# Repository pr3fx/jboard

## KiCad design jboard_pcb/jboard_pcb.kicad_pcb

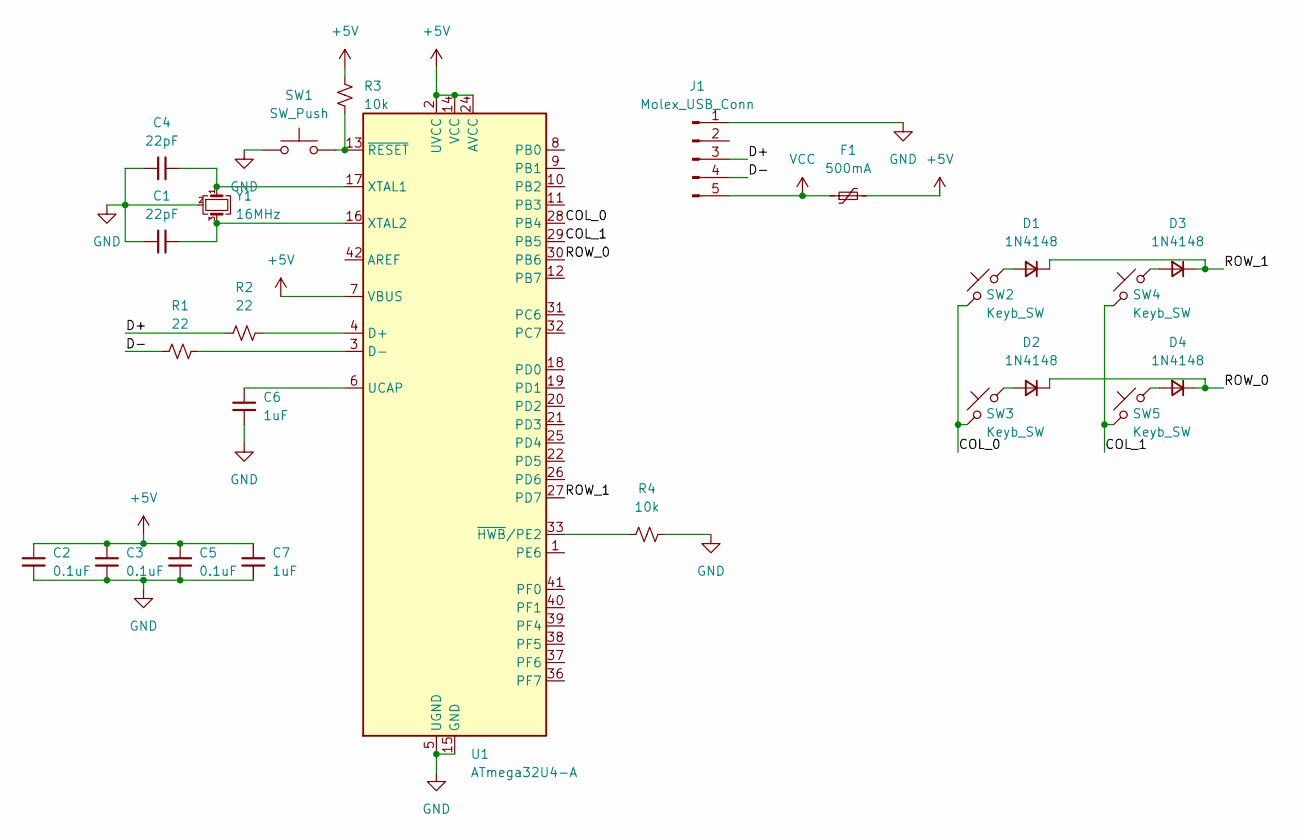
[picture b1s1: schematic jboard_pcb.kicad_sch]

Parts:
C1, C4: 22pF; C_0805_2012Metric
C2, C3, C5: 0.1uF; C_0805_2012Metric
C6, C7: 1uF; C_0805_2012Metric
D1, D2, D3, D4: 1N4148; D_SOD-123
F1: 500mA; Fuse_1206_3216Metric
J1: Molex_USB_Conn; Molex-0548190589
R1, R2: 22; R_0805_2012Metric
R3, R4: 10k; R_0805_2012Metric
SW1: SW_Push; SW_SPST_SKQG_WithoutStem
SW2, SW3, SW4, SW5: Keyb_SW; Kailh-PG1353-Solderable-1U
U1: ATmega32U4-A; TQFP-44_10x10mm_P0.8mm
Y1: 16MHz; Crystal_SMD_3225-4Pin_3.2x2.5mm

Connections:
+5V: C2.1, C3.1, C5.1, C7.1, F1.2, R3.1, U1.2 (UVCC), U1.7 (VBUS), U1.14 (VCC), U1.24 (AVCC), U1.34 (VCC), U1.44 (AVCC)
/COL_0: SW2.1, SW3.1, U1.28 (PB4)
/COL_1: SW4.1, SW5.1, U1.29 (PB5)
/D+: J1.3, R2.1
/D-: J1.4, R1.1
/ROW_0: D2.1 (K), D4.1 (K), U1.30 (PB6)
/ROW_1: D1.1 (K), D3.1 (K), U1.27 (PD7)
GND: C1.1, C2.2, C3.2, C4.1, C5.2, C6.2, C7.2, J1.1, R4.2, SW1.1, U1.5 (UGND), U1.15 (GND), U1.23 (GND), U1.35 (GND), U1.43 (GND), Y1.2 (G), Y1.4 (G)
unnamed: D1.2 (A), SW2.2
unnamed: D2.2 (A), SW3.2
unnamed: D3.2 (A), SW4.2
unnamed: D4.2 (A), SW5.2
unnamed: R2.2, U1.4 (D+)
unnamed: R1.2, U1.3 (D-)
unnamed: C6.1, U1.6 (UCAP)
unnamed: C4.2, U1.17 (XTAL1), Y1.1
unnamed: C1.2, U1.16 (XTAL2), Y1.3
unnamed: R4.1, U1.33 (~HWB/PE2)
unnamed: R3.2, SW1.2, U1.13 (~RESET)
VCC: F1.1, J1.5

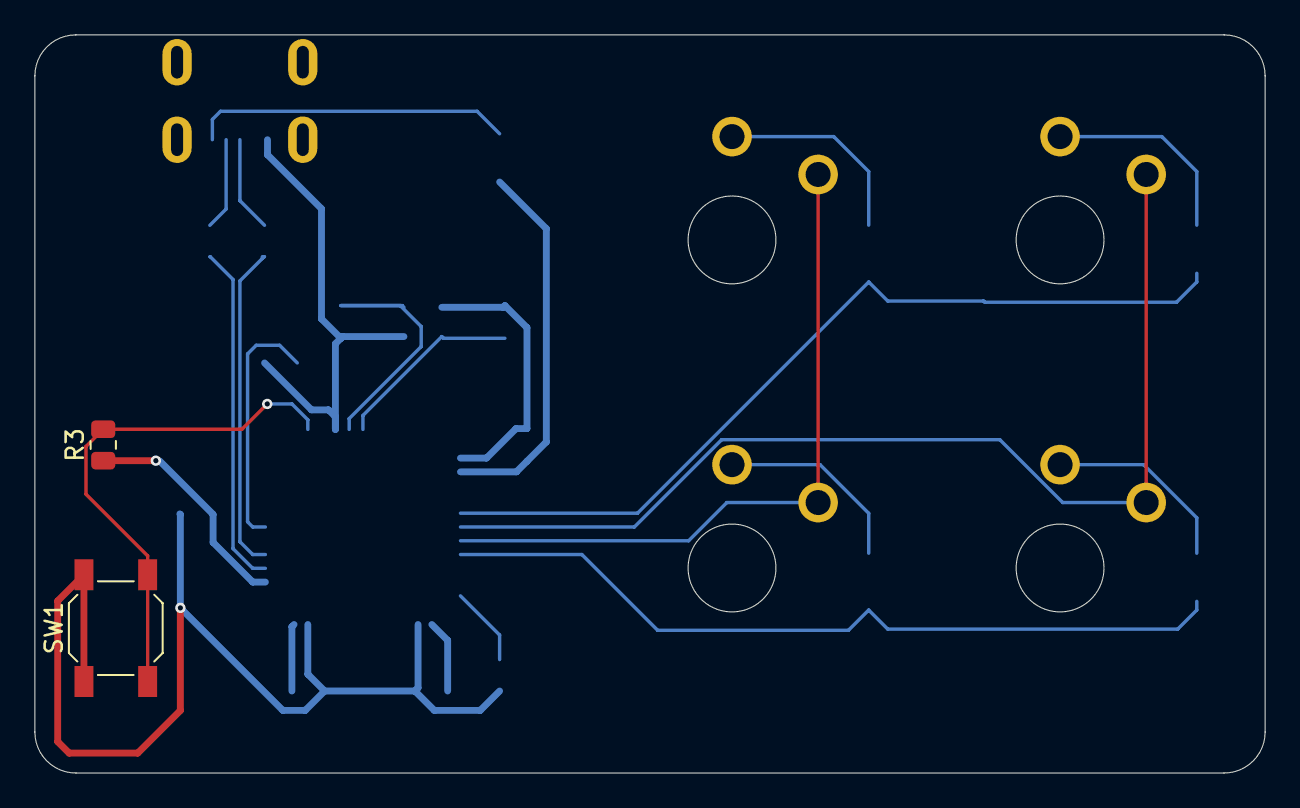
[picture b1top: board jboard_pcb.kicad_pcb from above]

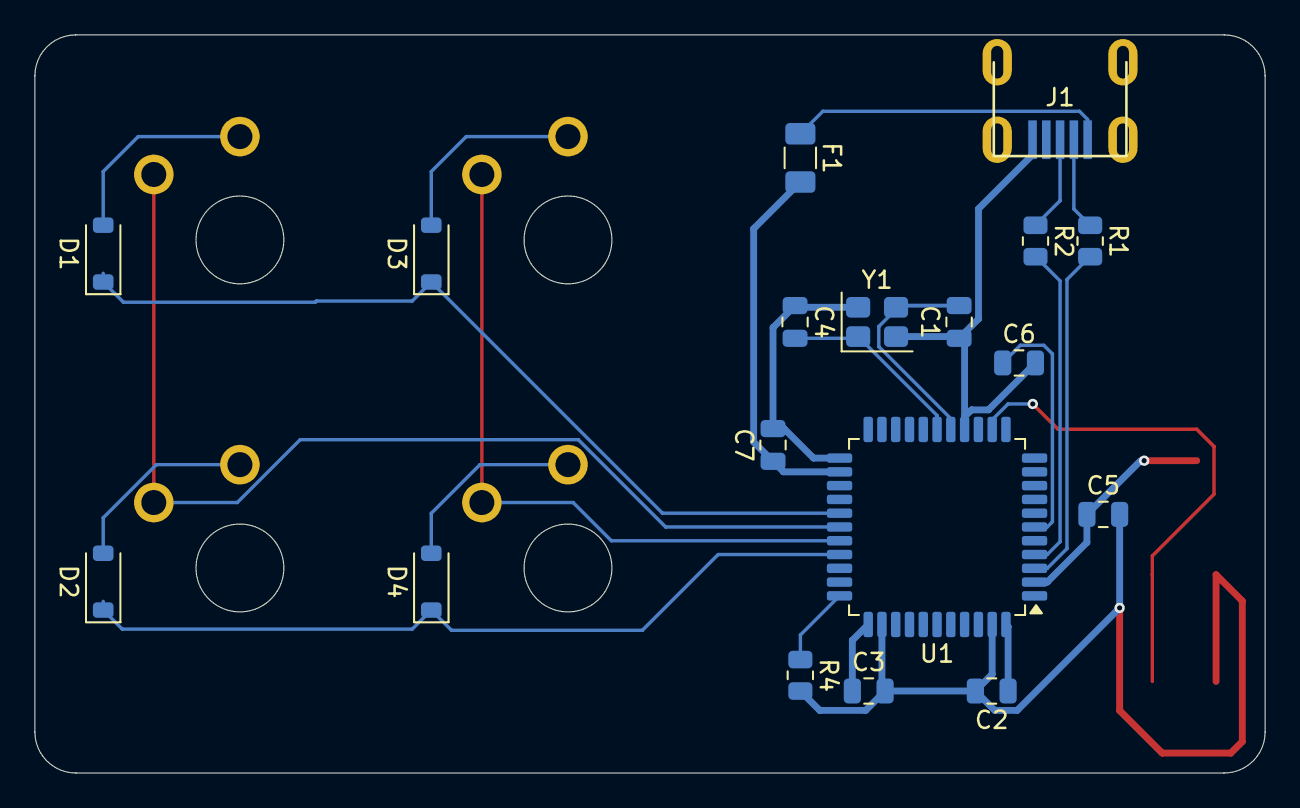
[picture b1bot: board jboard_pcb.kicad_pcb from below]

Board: 2 copper layers, 71.4 x 42.9 mm, 24 parts (18 on the bottom side), 20 nets.
